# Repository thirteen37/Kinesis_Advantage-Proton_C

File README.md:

# QMK-compatible replacement board for Kinesis Advantage

This replacement board allows you to use QMK on the [Kinesis Advantage
(KB500USB)](https://kinesis-ergo.com/support/advantage/).

This is the original version of the Kinesis Advantage and it lacks
much of the nice programmability and advanced features of the newer
[Advantage 2](https://kinesis-ergo.com/support/advantage2/) keyboards.

The replacement controller board here uses a [QMK Proton
C](https://qmk.fm/proton-c/). The replacement maintains the use of all
keys, all LEDs, and even the speaker for audio. You will also get to
replace the USB connector for a USB-C one. The only downside is that
the USB ports and optional foot pedals will not work here.

## Technical details

You can find details I reverse engineered in:

* [PCB Mechanicals](mechanical.md)
* [Wiring matrix](matrix.md)

## Assembly

### PCB Fabrication

The fabrication-ready files are in `plots/`. Just send them to your
preferred fab. It is a pretty standard 1.6mm PCB with conservative via
and track parameters that just about any shop can handle.

### Components

* 1x [QMK Proton C](https://qmk.fm/proton-c/)
* 4x [1.25mm Pitch Easy-On FFC/FPC
    Connectors](https://www.molex.com/molex/products/part-detail/ffc_fpc_connectors/0039532135)
* 4x 3mm T-1 LEDs (see LED chart)
* 4x axial through-hole resistors, 1/4W, 1% (see LED chart)
* 2.54mm "board-to-board" pin headers
  * 2x 12 pins
  * 2x 6 pins
  * 4x 10 pins
* 2x 2.54mm 8-pin IDC-IDC ribbon cables, 100mm length minimum
* 1x USB-C cable, 1M length minimum
* (Optional) 1x AST1109MLTRQ piezo speaker

#### LEDs

I used blue LEDs in my build for a distinctive appearance. You could
use other colors or even mix and match colors. You will have to use
different resistors for each type of LED.

The LEDs are powered from Vusb @ 5V, and the Proton C's pins operate
at 3.3V and can sink a decent amount of current, allowing for a fairly
wide selection of LEDs.

The following table is a guideline for some common LED values to
operate a maximum brightness. You should check your LED datasheet to
confirm.

| LED color      | LED voltage | LED current | Resistor |
|----------------|-------------|-------------|----------|
| Blue (472nm)   | 3.5V        | 20mA        | 75ohms   |
| Red (640nm)    | 1.8V        | 20mA        | 160ohms  |
| Yellow (590nm) | 2.0V        | 20mA        | 150ohms  |

### Steps

1. Disassemble keyboard
2. Replace existing ribbon cables
3. Assemble PCB
4. Re-assemble keyboard
5. Flash firmware and test

#### Disassemble keyboard

To Kinesis's credit, their keyboards are very easy to disassemble and
clean. There are six screws to remove from the bottom of the keyboard
to open it.

The USB cable is connected to a daughter board with the USB
ports. Separate the connector from the daughter board and remove the
retaining ring around the strain relief. This will allows you to
remove the USB cable completely. We will be running the new USB-C
cable through this hole. The daughter board will remain glued to the
bottom shell.

There is another cable that connects the daughter board to the main
controller board. I find it easier to remove the connector at the end
attached to the daughter board.

At this point, you can separate the bottom and top halves of the
keyboard.

You can detach the four flex cables from the main board. There is a
single retaining screw holding the main board down. Remove
this. Finally, remove the four screws on each thumb cluster. There is
a clamp on one of these screws holding the daughter board cable. Keep
this clamp as we will be reusing it later. You can now take out the
thumb cluster boards and the main board.

#### Replace ribbon cables

Unfortunately, the cables connecting the thumb clusters to the main
board are soldered. Instead of just reconnecting this to our new
board, we will replace them with pin headers and detachable cables.

It's easiest now to just cut the cables in half and desolder them from
each of the thumb clusters. Install the pin headers. They should be
facing the side opposite the key switches. I made the mistake of
soldering them on the wrong side, necessitating another tedious
desoldering.

#### Assemble PCB

I find it easiest to assemble the board in the following order:

1. Resistors
2. FPC connectors
3. Pin headers
4. LEDs
5. Proton C

Note the orientation of the FPC connectors. There is a notch on the
short edge closest to Pin 1 and this should correspond to the small
triangle on the footprint, or the square pad.

We are only installing header pins for the external rows of the Proton
C. You can ignore the internal pins. Do also solder the pin headers
for the thumb clusters.

The LEDs are installed on the reverse side of the PCB. Take care with
their alignment as they fit loosely on the PCB but have tighter
tolerances when installed into the plastic upper shell. As always,
orientation matters for diodes and Pin 1 (square pad) is for the
negative (shorter) leg.

The Proton C is the last component to be soldered. It should be
installed with the USB port facing away from the PCB and towards
you. If you want to use the optional speaker, solder it to the Proton
C before installing the Proton C to the main board.

#### Re-assemble keyboard

We are only using eight of the ten pins for each thumb cluster. Make
sure you connect pins 1-8 (Pin 1 has the square pad), leaving out pins
9-10 on both the thumb cluster and main board.

Don't forget to reinstall the clamp when attaching the screws for the
thumb clusters.

Finally, the USB C cable is plugged in to the Proton C. You will want
to loop it through the clamp to relieve strain on the Proton C
itself.

Before closing up the bottom and top shells, flash the firmware. You
will need access to the reset button on the Proton C for the first
time you flash.

#### Flash firmware and test

The corresponding QMK firmware for this can be found at
[thirteen37/qmk_firmware](https://github.com/thirteen37/qmk_firmware/tree/kinesis_thirteen37/keyboards/kinesis/thirteen37/README.md).

A compiled version can be found in `firmware/` for you to get started
quickly. Check the [instructions on the QMK
site](https://beta.docs.qmk.fm/using-qmk/guides/flashing/flashing#stm32)
on how to flash the firmware.

# Revisions

## 2020-06

* Initial version

## 2020-07

* Don't use `SWCLK` and `SWDIO` pins unless necessary
* Move LEDs to TIM4 pins (`PB6` - `PB9`)
* Routed using Freerouting

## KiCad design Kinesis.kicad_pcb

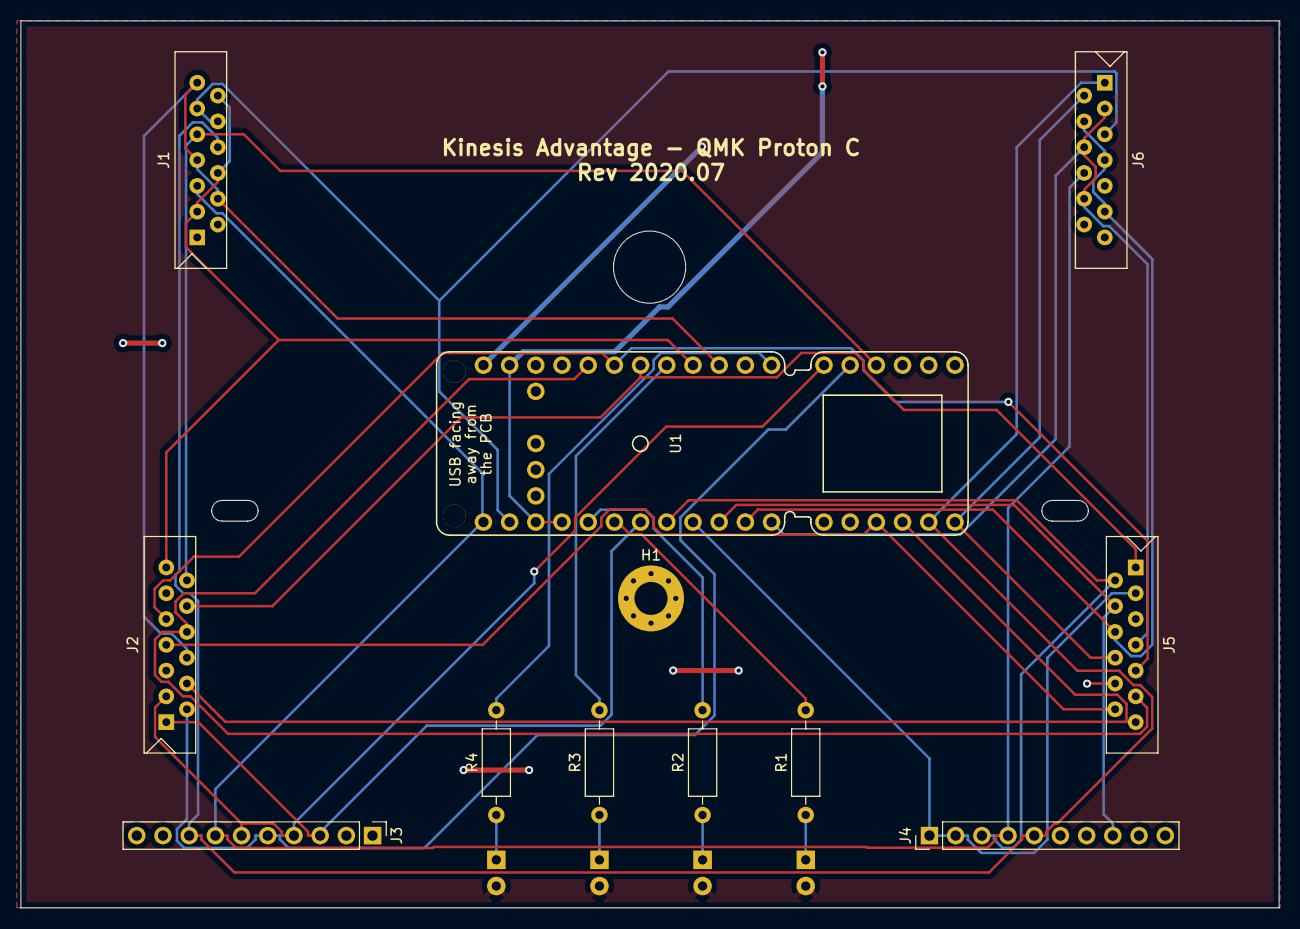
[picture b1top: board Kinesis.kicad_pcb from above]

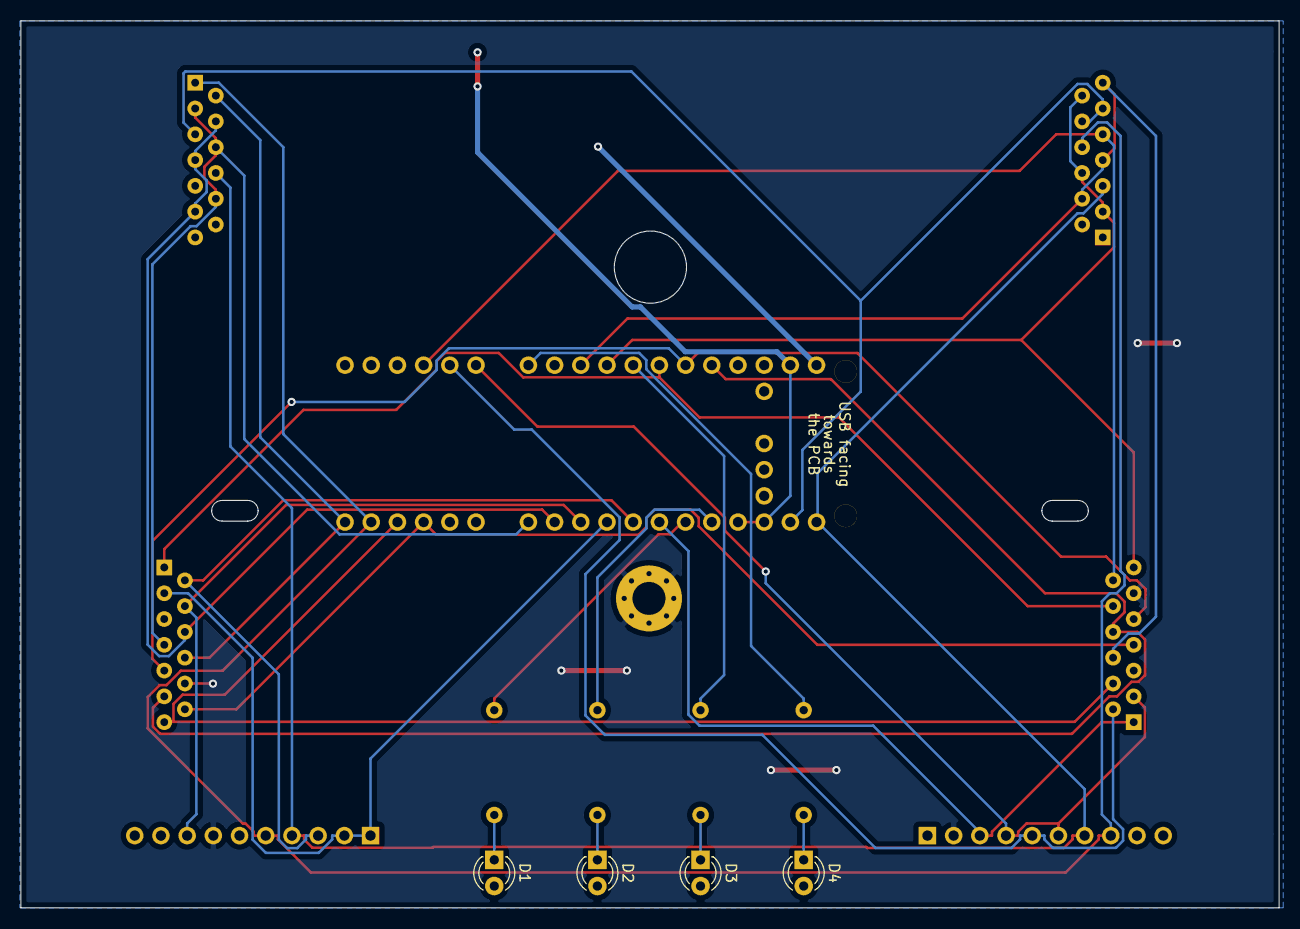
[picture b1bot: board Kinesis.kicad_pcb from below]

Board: 2 copper layers, 122.0 x 86.0 mm, 16 parts (4 on the bottom side), 30 nets.

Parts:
D1, D2, D3, D4: LED; LED_D3.0mm
H1: MountingHole_Pad; MountingHole_3.2mm_M3_Pad_Via
J1: Right Function; Molex_FFC-FPC_Easy-On_39-53-2135_13-Contact_Vertical
J2: Right Main; Molex_FFC-FPC_Easy-On_39-53-2135_13-Contact_Vertical
J3: Right Thumb; PinHeader_1x10_P2.54mm_Vertical
J4: Left Thumb; PinHeader_1x10_P2.54mm_Vertical
J5: Left Main; Molex_FFC-FPC_Easy-On_39-53-2135_13-Contact_Vertical
J6: Left Function; Molex_FFC-FPC_Easy-On_39-53-2135_13-Contact_Vertical
R1, R2, R3, R4: 75ohms; R_Axial_DIN0207_L6.3mm_D2.5mm_P10.16mm_Horizontal
U1: proton_c

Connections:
GND: H1.1, J2.11, J3.2, J4.7, J5.10
unnamed: D1.1, R1.1
unnamed: D1.2, D2.2, D3.2, D4.2, U1.5V
unnamed: D2.1, R2.1
unnamed: D3.1, R3.1
unnamed: D4.1, R4.1
unnamed: J1.5, J3.7, J4.4, J6.8, U1.A9
unnamed: J1.8, J3.8, J4.5, J6.1, U1.A8
unnamed: J1.9, J2.12, U1.B12
unnamed: J1.10, J1.11, J6.5, U1.A10
unnamed: J1.3, J1.6, J1.12, J2.13, U1.B13
unnamed: J1.4, J1.7, J1.13, J2.6, U1.B14
unnamed: J2.1, J3.3, U1.B5
unnamed: J2.2, J3.5, U1.B11
unnamed: J2.3, J3.4, J3.6, U1.B10
unnamed: J2.4, J5.13, U1.A7
unnamed: J2.7, J5.12, U1.A6
unnamed: J2.8, J5.11, U1.A2
unnamed: J2.9, J5.9, U1.A1
unnamed: J2.10, J5.1, U1.A0
unnamed: J4.1, J4.2, J5.3, U1.B3
unnamed: J4.3, J5.2, U1.B4
unnamed: J4.8, J5.4, U1.B2
unnamed: J5.6, J6.4, J6.7, J6.11, U1.B1
unnamed: J5.7, J6.3, J6.6, J6.10, U1.B0
unnamed: J5.8, J6.2, U1.A15
unnamed: R1.2, U1.B6
unnamed: R2.2, U1.B7
unnamed: R3.2, U1.B8
unnamed: R4.2, U1.B9

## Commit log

2020-06-10 Squashed 'libs/qmk_hardware/' content from commit 64f0be6
    git-subtree-dir: libs/qmk_hardware
    git-subtree-split: 64f0be61e7f44833726313cccbe1bc0ecc0afbe8
2020-06-10 Fix module libraries
2020-06-10 .gitignore
2020-06-10 Basic README and reverse engineering details
2020-06-10 Link to hardware
2020-06-10 PCB components
2020-06-10 Add resistor chart
2020-06-10 First part of instructions
2020-06-10 Next part of assembly instructions
2020-06-11 Additional instructions
2020-06-11 PCB fab instructions and images
2020-06-11 Firmware flashing instructions
2020-06-11 Add firmware file
2020-06-11 Additional images
2020-06-11 Annotated images
2020-06-11 Fix thumb cluster image
2020-06-11 Fix Molex footprints
2020-06-12 Use TIM4 for LEDs
    Also free up debug pins
2020-06-12 Update images
2020-06-13 Add cabling diagram
2021-03-19 Bump pillow from 4.3.0 to 8.1.1 in /libs/qmk_hardware/tools
    Bumps [pillow](https://github.com/python-pillow/Pillow) from 4.3.0 to 8.1.1.
    - [Release notes](https://github.com/python-pillow/Pillow/releases)
    - [Changelog](https://github.com/python-pillow/Pillow/blob/master/CHANGES.rst)
    - [Commits](https://github.com/python-pillow/Pillow/compare/4.3.0...8.1.1)
2021-06-08 Bump pillow from 4.3.0 to 8.2.0 in /libs/qmk_hardware/tools
    Bumps [pillow](https://github.com/python-pillow/Pillow) from 4.3.0 to 8.2.0.
    - [Release notes](https://github.com/python-pillow/Pillow/releases)
    - [Changelog](https://github.com/python-pillow/Pillow/blob/master/CHANGES.rst)
    - [Commits](https://github.com/python-pillow/Pillow/compare/4.3.0...8.2.0)
    ---
    updated-dependencies:
2021-11-11 Squashed 'libs/qmk_hardware/' changes from 64f0be6..819b22b
    819b22b Merge pull request #15 from qmk/dependabot/pip/tools/pillow-8.2.0
    1bb7bc9 Bump pillow from 4.3.0 to 8.2.0 in /tools
    git-subtree-dir: libs/qmk_hardware
    git-subtree-split: 819b22b92f7af715336042deea8cb002d6f68580
2021-11-11 Bump pillow from 4.3.0 to 8.3.2 in /libs/qmk_hardware/tools
    Bumps [pillow](https://github.com/python-pillow/Pillow) from 4.3.0 to 8.3.2.
    - [Release notes](https://github.com/python-pillow/Pillow/releases)
    - [Changelog](https://github.com/python-pillow/Pillow/blob/master/CHANGES.rst)
    - [Commits](https://github.com/python-pillow/Pillow/compare/4.3.0...8.3.2)
    ---
    updated-dependencies:
2022-01-13 Bump pillow from 8.2.0 to 9.0.0 in /libs/qmk_hardware/tools
    Bumps [pillow](https://github.com/python-pillow/Pillow) from 8.2.0 to 9.0.0.
    - [Release notes](https://github.com/python-pillow/Pillow/releases)
    - [Changelog](https://github.com/python-pillow/Pillow/blob/main/CHANGES.rst)
    - [Commits](https://github.com/python-pillow/Pillow/compare/8.2.0...9.0.0)
    ---
    updated-dependencies:
2022-03-12 Bump pillow from 8.2.0 to 9.0.1 in /libs/qmk_hardware/tools
    Bumps [pillow](https://github.com/python-pillow/Pillow) from 8.2.0 to 9.0.1.
    - [Release notes](https://github.com/python-pillow/Pillow/releases)
    - [Changelog](https://github.com/python-pillow/Pillow/blob/main/CHANGES.rst)
    - [Commits](https://github.com/python-pillow/Pillow/compare/8.2.0...9.0.1)
    ---
    updated-dependencies:
2022-06-22 Bump numpy from 1.13.3 to 1.22.0 in /libs/qmk_hardware/tools
    Bumps [numpy](https://github.com/numpy/numpy) from 1.13.3 to 1.22.0.
    - [Release notes](https://github.com/numpy/numpy/releases)
    - [Changelog](https://github.com/numpy/numpy/blob/main/doc/HOWTO_RELEASE.rst)
    - [Commits](https://github.com/numpy/numpy/compare/v1.13.3...v1.22.0)
    ---
    updated-dependencies:
2022-11-22 Bump pillow from 8.2.0 to 9.3.0 in /libs/qmk_hardware/tools
    Bumps [pillow](https://github.com/python-pillow/Pillow) from 8.2.0 to 9.3.0.
    - [Release notes](https://github.com/python-pillow/Pillow/releases)
    - [Changelog](https://github.com/python-pillow/Pillow/blob/main/CHANGES.rst)
    - [Commits](https://github.com/python-pillow/Pillow/compare/8.2.0...9.3.0)
    ---
    updated-dependencies:
2023-10-03 Bump pillow from 8.2.0 to 10.0.1 in /libs/qmk_hardware/tools
    Bumps [pillow](https://github.com/python-pillow/Pillow) from 8.2.0 to 10.0.1.
    - [Release notes](https://github.com/python-pillow/Pillow/releases)
    - [Changelog](https://github.com/python-pillow/Pillow/blob/main/CHANGES.rst)
    - [Commits](https://github.com/python-pillow/Pillow/compare/8.2.0...10.0.1)
    ---
    updated-dependencies:
